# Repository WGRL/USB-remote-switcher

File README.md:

# USB REMOTE SWITCHER
USB hub with multiple USB-A inputs and one USB-C pc output. Active port is remotely chosen using remote communication between two esp32c6 boards.
# SCHEMATICS
The schematics for the hub board.

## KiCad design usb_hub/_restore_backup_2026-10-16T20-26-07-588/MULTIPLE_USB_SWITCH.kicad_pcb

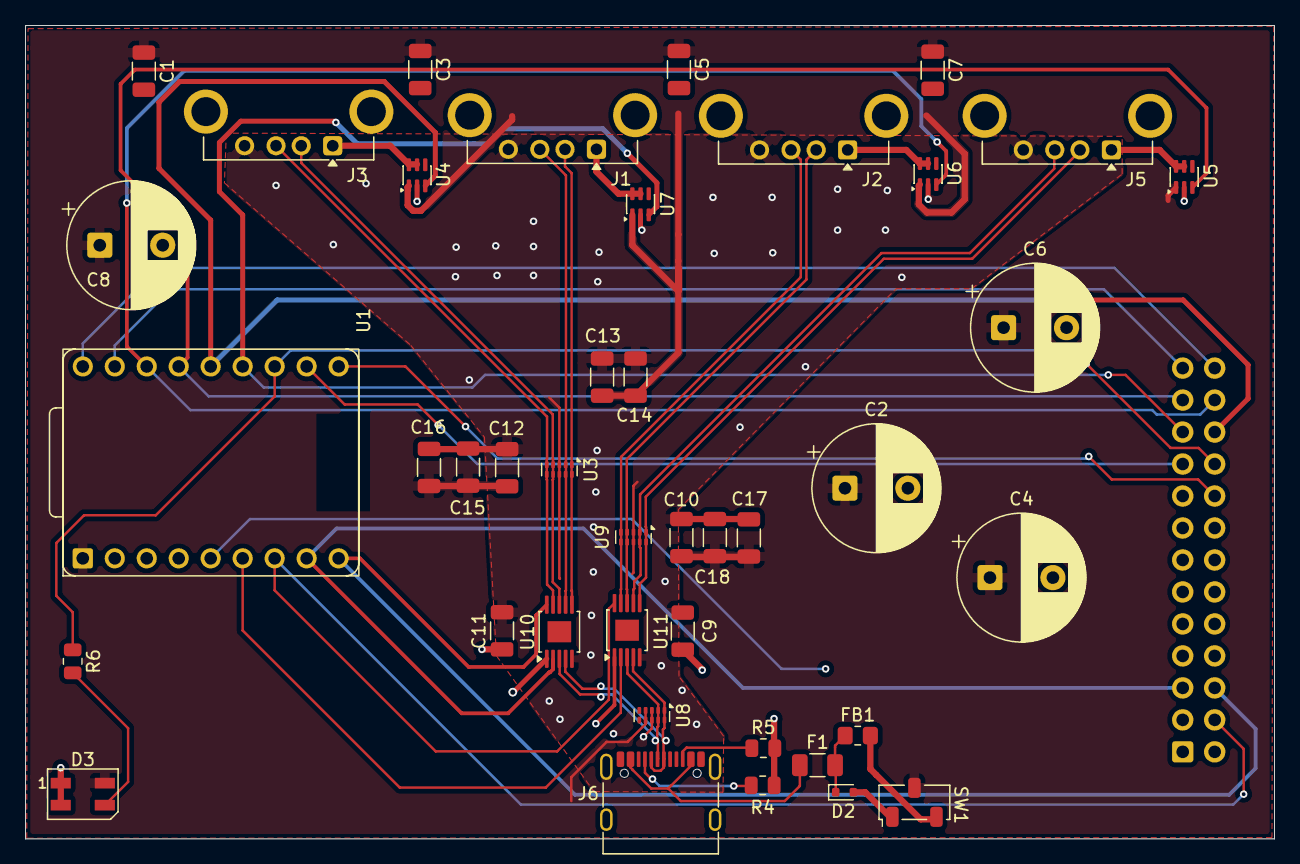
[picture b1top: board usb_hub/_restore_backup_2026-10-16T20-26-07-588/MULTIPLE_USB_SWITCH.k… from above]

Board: 4 copper layers, 99.2 x 64.6 mm, 42 parts (1 on the bottom side), 38 nets.

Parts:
C1, C3, C5, C7, C9, C10, C11, C12, C13, C14: 100n; C_1206_3216Metric
C2, C4, C6, C8: 220u; CP_Radial_D10.0mm_P5.00mm
C15, C16, C17, C18: 47u; C_1206_3216Metric
D2: 5V; D_SOD-523
D3: SK6812MINI; LED_SK6812MINI_PLCC4_3.5x3.5mm_P1.75mm
F1: 2A; Fuse_1206_3216Metric
FB1: 220Ω@100MHz; R_0805_2012Metric_Pad1.20x1.40mm_HandSolder
J1, J2, J3, J5: USB_A; USB_A_Connfly_DS1095
J6: USB_C_Receptacle_USB2.0_16P; USB_C_Receptacle_G-Switch_GT-USB-7010ASV
J7: Conn_02x13_Counter_Clockwise_MountingPin; IDC-Header_2x13_P2.54mm_Vertical
R4, R5: 5k1; R_0805_2012Metric
R6: 200; R_0805_2012Metric
SW1: SW_Nidec_CAS-120A1; Nidec_Copal_CAS-120A
U1: ESP32-C3; Waveshare_ESP32_S3_Zero_THT
U3, U8: D3V3XA4B10LP; USON-10_2.5x1.0mm_P0.5mm
U4, U5, U6, U7: TPS22919DCK; SOT-363_SC-70-6
U9: D3V3X4U10LP; USON-10_2.5x1.0mm_P0.5mm
U10, U11: FSUSB42; MSOP-10-1EP_3x3mm_P0.5mm_EP1.68x1.88mm

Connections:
3V3: C9.1, C11.1, J7.14, J7.15, J7.16, J7.17, U1.3 (3V3), U10.1 (VCC), U11.1 (VCC)
+5V: FB1.2, SW1.3 (A)
/main_components/GPIO0: J7.1, U1.4 (gpio0)
/main_components/GPIO1: J7.2, U1.5 (gpio1)
/main_components/GPIO6: J7.18, U1.10 (gpio6)
/main_components/GPIO7: J7.19, U1.11 (gpio7)
/main_components/GPIO20: J7.25, U1.17 (gpio20)
/main_components/GPIO21: J7.26, U1.18 (gpio21)
/main_components/LED_DIN: J7.20, R6.1, U1.12 (gpio8)
/main_components/MUX0: J7.5, U1.8 (gpio4), U10.2 (SEL)
/main_components/MUX1: J7.6, U1.9 (gpio5), U10.10 (~OE)
/main_components/MUX2: J7.3, U1.6 (gpio2), U11.2 (SEL)
/main_components/MUX3: J7.4, U1.7 (gpio3), U11.10 (~OE)
/main_components/ON_0: J7.21, U1.13 (gpio9), U7.3 (ON)
/main_components/ON_1: J7.22, U1.14 (gpio10), U4.3 (ON)
/main_components/ON_2: J7.23, U1.15 (gpio18), U5.3 (ON)
/main_components/ON_3: J7.24, U1.16 (gpio19), U6.3 (ON)
D0+: J1.3 (D+), U3.2, U3.9 (NC), U10.7 (HSD1+)
D0-: J1.2 (D-), U3.1, U3.10 (NC), U10.6 (HSD1-)
D1+: J3.3 (D+), U3.5, U3.6 (NC), U10.9 (HSD2+)
D1-: J3.2 (D-), U3.4, U3.7 (NC), U10.8 (HSD2-)
D2+: J5.3 (D+), U9.2, U9.9 (NC), U11.7 (HSD1+)
D2-: J5.2 (D-), U9.1, U9.10 (NC), U11.6 (HSD1-)
D3+: J2.3 (D+), U9.5, U9.6 (NC), U11.9 (HSD2+)
D3-: J2.2 (D-), U9.4, U9.7 (NC), U11.8 (HSD2-)
D+: J6.A6 (D+), J6.B6 (D+), U8.2, U8.9 (NC), U10.3 (D+), U11.3 (D+)
D-: J6.A7 (D-), J6.B7 (D-), U8.1, U8.10 (NC), U10.4 (D-), U11.4 (D-)
GND: C1.2, C2.2, C3.2, C4.2, C5.2, C6.2, C7.2, C8.2, C9.2, C10.2, C11.2, C12.2, C13.2, C14.2, C15.2, C16.2, C17.2, C18.2, D2.2 (A2), D3.1 (DOUT), D3.2 (VSS), J1.4 (GND), J1.SH (Shield), J2.4 (GND), J2.SH (Shield), J3.4 (GND), J3.SH (Shield), J5.4 (GND), J5.SH (Shield), J6.A1 (GND), J6.A12 (GND), J6.B1 (GND), J6.B12 (GND), J6.SH (SHIELD), J7.7, J7.8, J7.9, J7.10, J7.11, J7.12, J7.13, R4.2, R5.2, SW1.1 (C), U1.2 (GND), U3.3 (VSS), U3.8 (VSS), U4.2 (GND), U5.2 (GND), U6.2 (GND), U7.2 (GND), U8.3 (VSS), U8.8 (VSS), U9.3 (VSS), U9.8 (VSS), U10.5 (GND), U11.5 (GND)
unnamed: D2.1 (A1), F1.2, FB1.1
unnamed: D3.3 (DIN), R6.2
unnamed: F1.1, J6.A4 (VBUS), J6.A9 (VBUS), J6.B4 (VBUS), J6.B9 (VBUS)
unnamed: J6.A5 (CC1), R4.1
unnamed: J6.B5 (CC2), R5.1
VCC: C1.1, C2.1, C3.1, C4.1, C5.1, C6.1, C7.1, C8.1, C10.1, C12.1, C13.1, C14.1, C15.1, C16.1, C17.1, C18.1, D3.4 (VDD), SW1.2 (B), U1.1 (5V), U4.1 (IN), U5.1 (IN), U6.1 (IN), U7.1 (IN), U8.4, U8.7 (NC)
V_USB0: J1.1 (VBUS), U7.5 (QOD), U7.6 (OUT)
V_USB1: J3.1 (VBUS), U4.5 (QOD), U4.6 (OUT)
V_USB2: J5.1 (VBUS), U5.5 (QOD), U5.6 (OUT)
V_USB3: J2.1 (VBUS), U6.5 (QOD), U6.6 (OUT)

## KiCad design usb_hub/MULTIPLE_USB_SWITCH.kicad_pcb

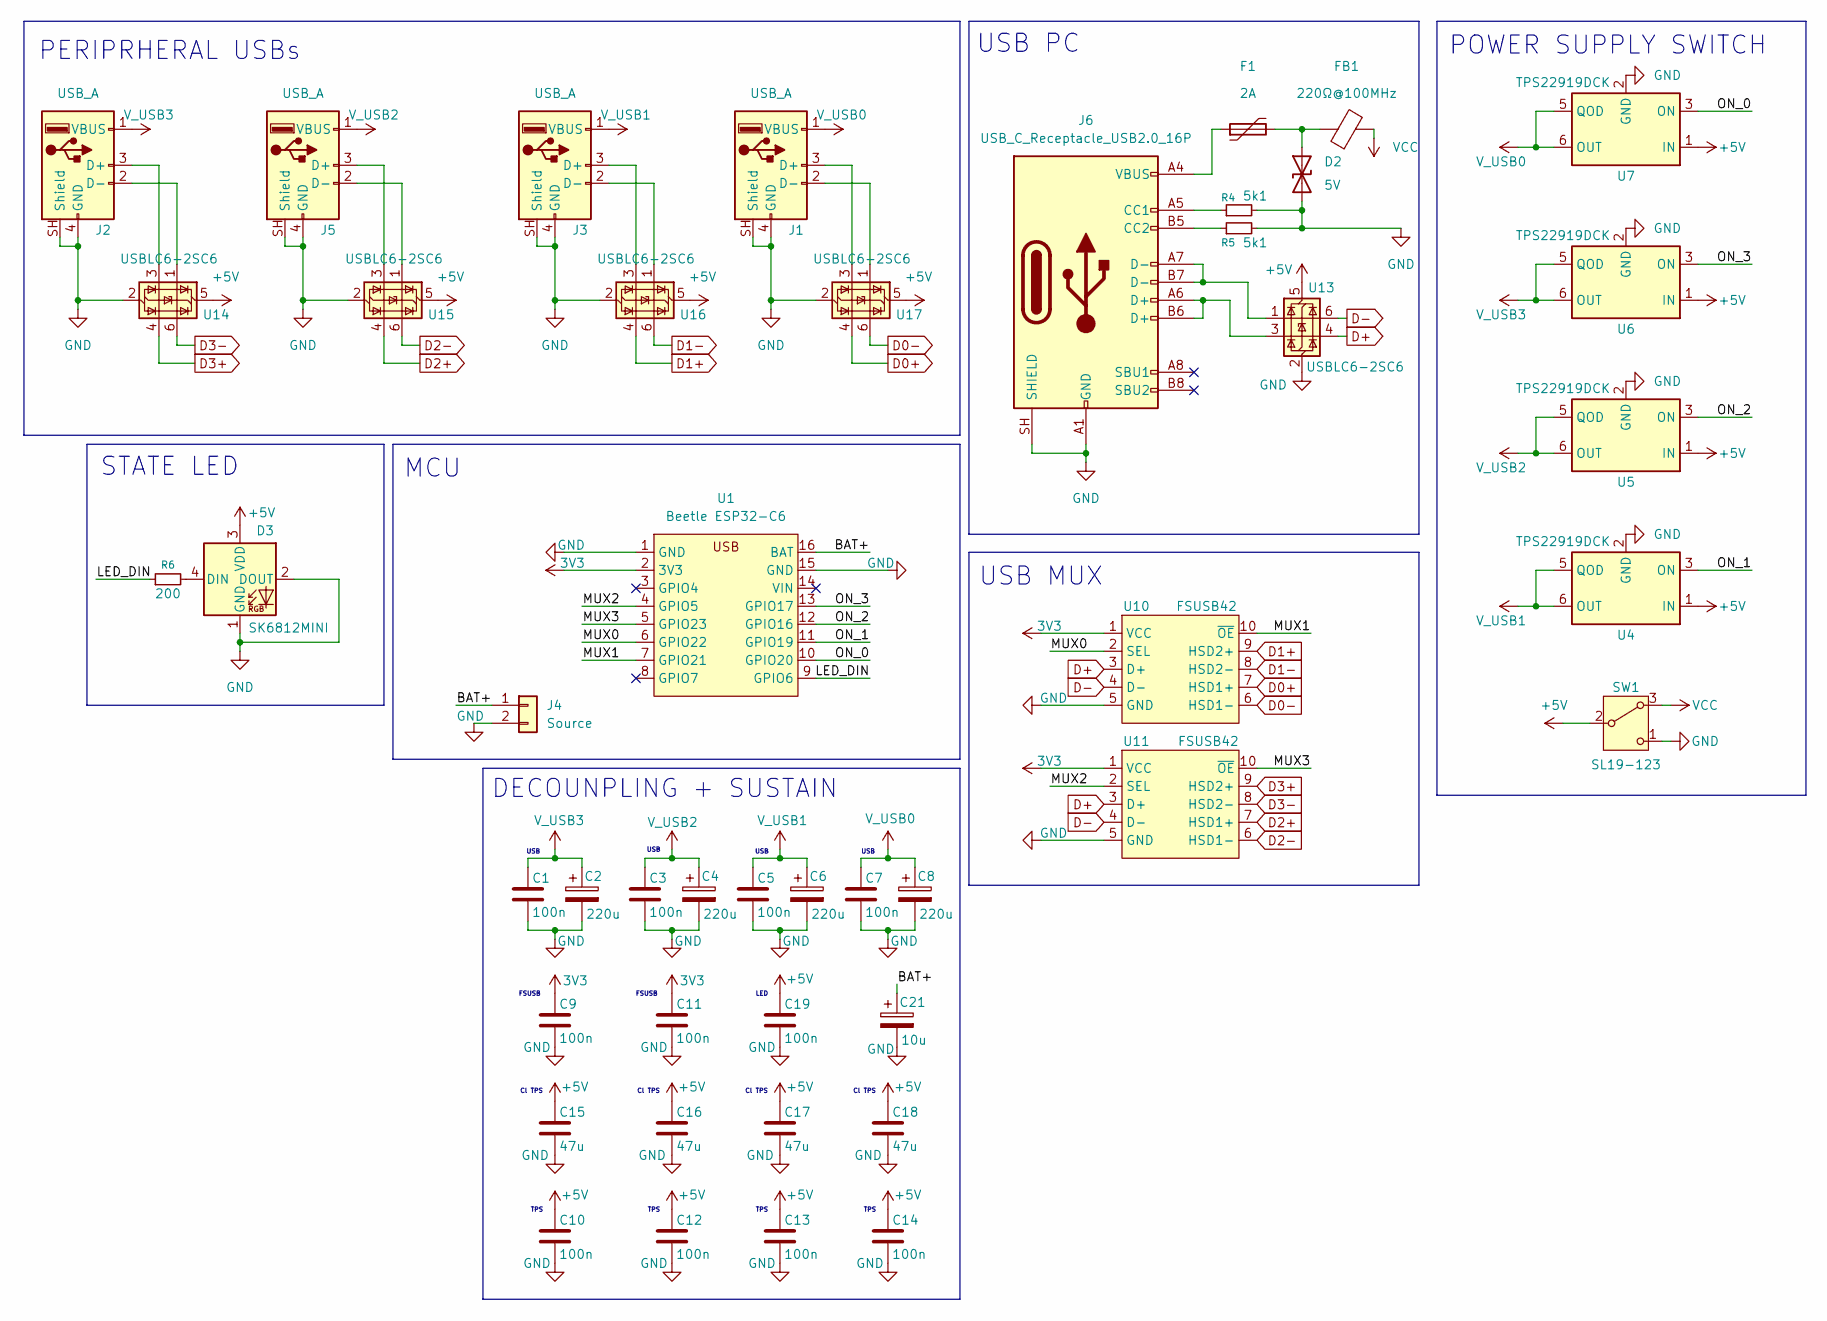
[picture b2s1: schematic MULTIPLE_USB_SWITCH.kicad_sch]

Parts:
C1, C3, C5, C7, C9, C10, C11, C12, C13, C14, C19: 100n; C_0805_2012Metric
C2, C4, C6, C8: 220u; CP_Radial_D8.0mm_P3.50mm
C15, C16, C17, C18: 47u; CP_Elec_5x5.3
C21: 10u; CP_Radial_D5.0mm_P2.00mm
D2: 5V; D_SMB; LCSC Part # C82044
D3: SK6812MINI; PL9823-F8
F1: 2A; Fuse_1206_3216Metric; LCSC Part # C883135
FB1: 220Ω@100MHz; R_0805_2012Metric_Pad1.20x1.40mm_HandSolder; LCSC Part # C85840
J1, J2, J3, J5: USB_A; USB_A_Connfly_DS1095
J4: Source; JST_XH_B2B-XH-A_1x02_P2.50mm_Vertical
J6: USB_C_Receptacle_USB2.0_16P; USB_C_Receptacle_G-Switch_GT-USB-7010ASV
R4, R5: 5k1; R_0805_2012Metric
R6: 200; R_0805_2012Metric
SW1: SL19-123; slider
U1: Beetle ESP32-C6
U4, U5, U6, U7: TPS22919DCK; SOT-363_SC-70-6
U10, U11: FSUSB42; MSOP-10-1EP_3x3mm_P0.5mm_EP1.68x1.88mm
U13, U14, U15, U16, U17: USBLC6-2SC6; SOT-23-6

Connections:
3V3: C9.1, C11.1, U1.2 (3V3), U10.1 (VCC), U11.1 (VCC)
+5V: C10.1, C12.1, C13.1, C14.1, C15.1, C16.1, C17.1, C18.1, C19.1, D3.3 (VDD), SW1.2 (B), U4.1 (IN), U5.1 (IN), U6.1 (IN), U7.1 (IN), U13.5 (VBUS), U14.5 (VBUS), U15.5 (VBUS), U16.5 (VBUS), U17.5 (VBUS)
/main_components/BAT+: C21.1, J4.1, U1.16 (BAT)
/main_components/LED_DIN: R6.1, U1.9 (GPIO6)
/main_components/MUX0: U1.6 (GPIO22), U10.2 (SEL)
/main_components/MUX1: U1.7 (GPIO21), U10.10 (~OE)
/main_components/MUX2: U1.4 (GPIO5), U11.2 (SEL)
/main_components/MUX3: U1.5 (GPIO23), U11.10 (~OE)
/main_components/ON_0: U1.10 (GPIO20), U7.3 (ON)
/main_components/ON_1: U1.11 (GPIO19), U4.3 (ON)
/main_components/ON_2: U1.12 (GPIO16), U5.3 (ON)
/main_components/ON_3: U1.13 (GPIO17), U6.3 (ON)
D0+: U10.7 (HSD1+), U17.4 (I/O2)
D0-: U10.6 (HSD1-), U17.6 (I/O1)
D1+: U10.9 (HSD2+), U16.4 (I/O2)
D1-: U10.8 (HSD2-), U16.6 (I/O1)
D2+: U11.7 (HSD1+), U15.4 (I/O2)
D2-: U11.6 (HSD1-), U15.6 (I/O1)
D3+: U11.9 (HSD2+), U14.4 (I/O2)
D3-: U11.8 (HSD2-), U14.6 (I/O1)
D+: U10.3 (D+), U11.3 (D+), U13.4 (I/O2)
D-: U10.4 (D-), U11.4 (D-), U13.6 (I/O1)
GND: C1.2, C2.2, C3.2, C4.2, C5.2, C6.2, C7.2, C8.2, C9.2, C10.2, C11.2, C12.2, C13.2, C14.2, C15.2, C16.2, C17.2, C18.2, C19.2, C21.2, D2.2 (A2), D3.1 (GND), D3.2 (DOUT), J1.4 (GND), J1.SH (Shield), J2.4 (GND), J2.SH (Shield), J3.4 (GND), J3.SH (Shield), J4.2, J5.4 (GND), J5.SH (Shield), J6.A1 (GND), J6.A12 (GND), J6.B1 (GND), J6.B12 (GND), J6.SH (SHIELD), R4.2, R5.2, SW1.1 (C), U1.1 (GND), U1.15 (GND), U4.2 (GND), U5.2 (GND), U6.2 (GND), U7.2 (GND), U10.5 (GND), U11.5 (GND), U13.2 (GND), U14.2 (GND), U15.2 (GND), U16.2 (GND), U17.2 (GND)
unnamed: D2.1 (A1), F1.2, FB1.1
unnamed: D3.4 (DIN), R6.2
unnamed: F1.1, J6.A4 (VBUS), J6.A9 (VBUS), J6.B4 (VBUS), J6.B9 (VBUS)
unnamed: J1.3 (D+), U17.3 (I/O2)
unnamed: J1.2 (D-), U17.1 (I/O1)
unnamed: J2.3 (D+), U14.3 (I/O2)
unnamed: J2.2 (D-), U14.1 (I/O1)
unnamed: J3.3 (D+), U16.3 (I/O2)
unnamed: J3.2 (D-), U16.1 (I/O1)
unnamed: J5.3 (D+), U15.3 (I/O2)
unnamed: J5.2 (D-), U15.1 (I/O1)
unnamed: J6.A5 (CC1), R4.1
unnamed: J6.B5 (CC2), R5.1
unnamed: J6.A6 (D+), J6.B6 (D+), U13.3 (I/O2)
unnamed: J6.A7 (D-), J6.B7 (D-), U13.1 (I/O1)
VCC: FB1.2, SW1.3 (A)
V_USB0: C7.1, C8.1, J1.1 (VBUS), U7.5 (QOD), U7.6 (OUT)
V_USB1: C5.1, C6.1, J3.1 (VBUS), U4.5 (QOD), U4.6 (OUT)
V_USB2: C3.1, C4.1, J5.1 (VBUS), U5.5 (QOD), U5.6 (OUT)
V_USB3: C1.1, C2.1, J2.1 (VBUS), U6.5 (QOD), U6.6 (OUT)

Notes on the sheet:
PERIPRHERAL USBs
STATE LED
Cl TPS
LED
FSUSB
POWER SUPPLY SWITCH
USB
TPS
MCU
DECOUNPLING + SUSTAIN
USB PC
USB MUX

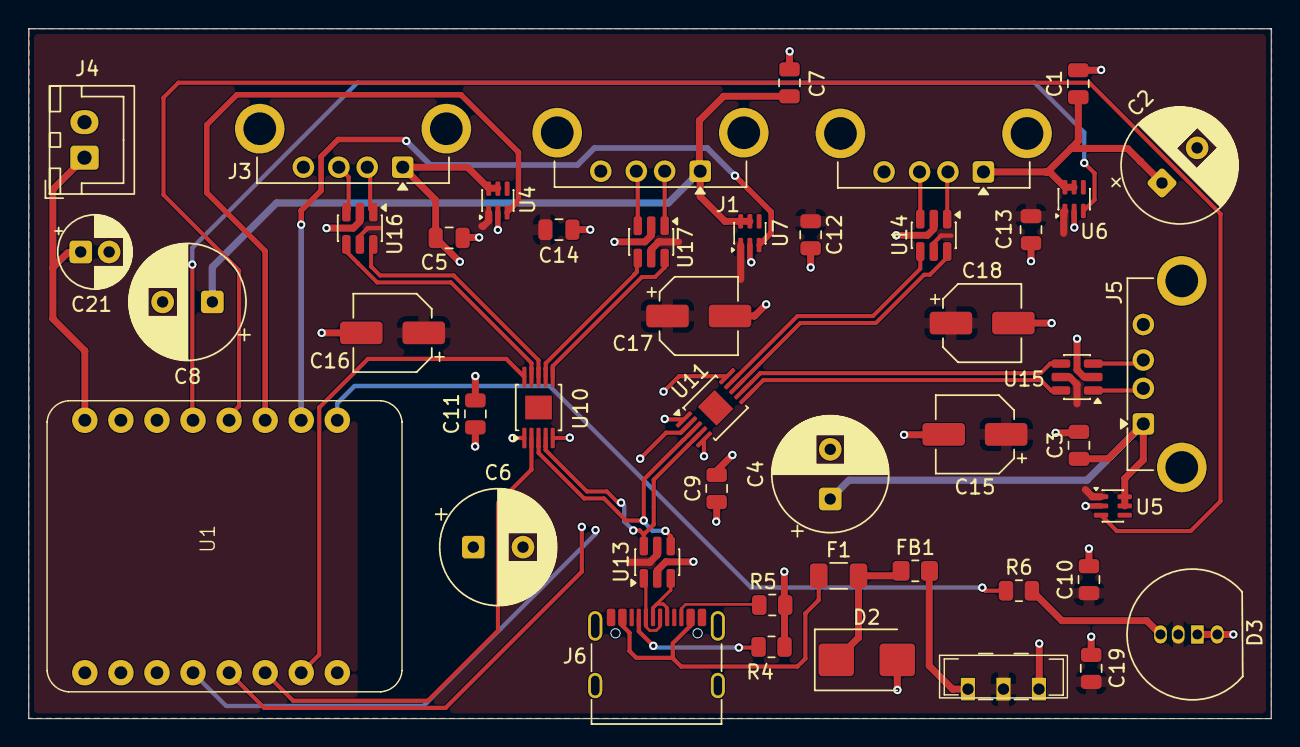
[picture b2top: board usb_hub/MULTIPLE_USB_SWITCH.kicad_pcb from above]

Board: 4 copper layers, 87.5 x 48.6 mm, 46 parts (0 on the bottom side), 43 nets.

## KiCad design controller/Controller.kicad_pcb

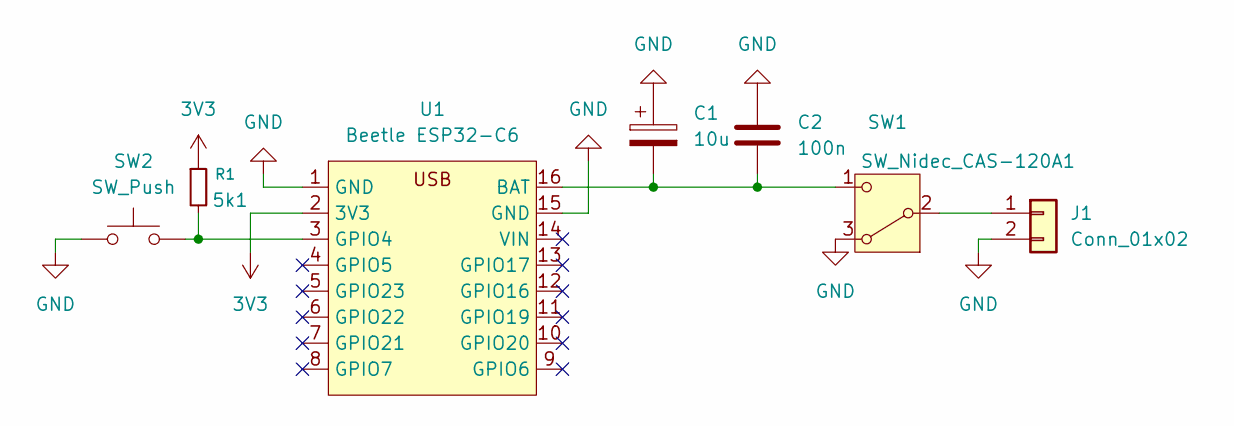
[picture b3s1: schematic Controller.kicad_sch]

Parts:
C1: 10u; CP_Radial_D5.0mm_P2.00mm
C2: 100n; C_0805_2012Metric
J1: Conn_01x02; JST_XH_B2B-XH-A_1x02_P2.50mm_Vertical
R1: 5k1; R_0805_2012Metric
SW1: SW_Nidec_CAS-120A1; slider
SW2: SW_Push; SW_PUSH_6mm
U1: Beetle ESP32-C6

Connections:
3V3: R1.1, U1.2 (3V3)
GND: C1.1, C2.1, J1.2, SW1.3 (A), SW2.1, U1.1 (GND), U1.15 (GND)
unnamed: J1.1, SW1.2 (B)
unnamed: C1.2, C2.2, SW1.1 (C), U1.16 (BAT)
unnamed: R1.2, SW2.2, U1.3 (GPIO4)

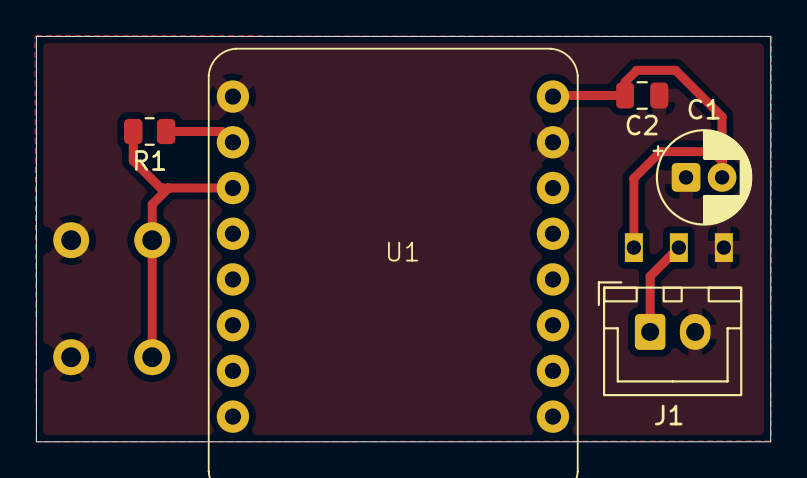
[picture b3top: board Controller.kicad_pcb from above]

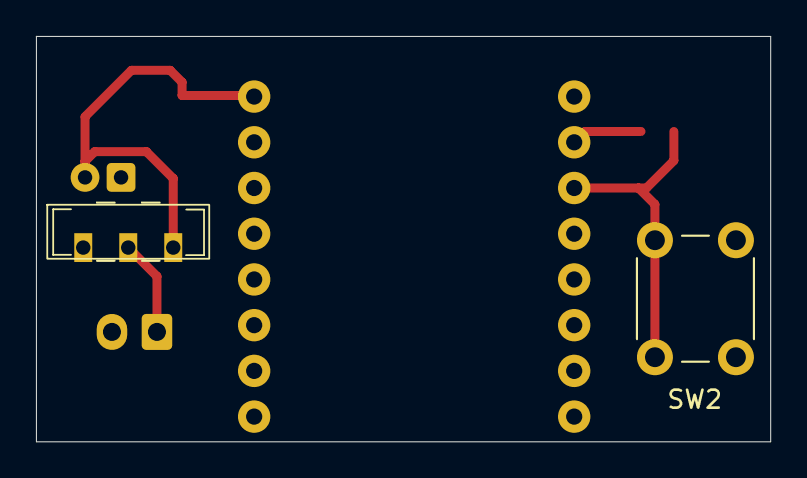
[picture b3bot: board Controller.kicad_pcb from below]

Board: 2 copper layers, 40.8 x 22.5 mm, 7 parts (2 on the bottom side), 5 nets.
